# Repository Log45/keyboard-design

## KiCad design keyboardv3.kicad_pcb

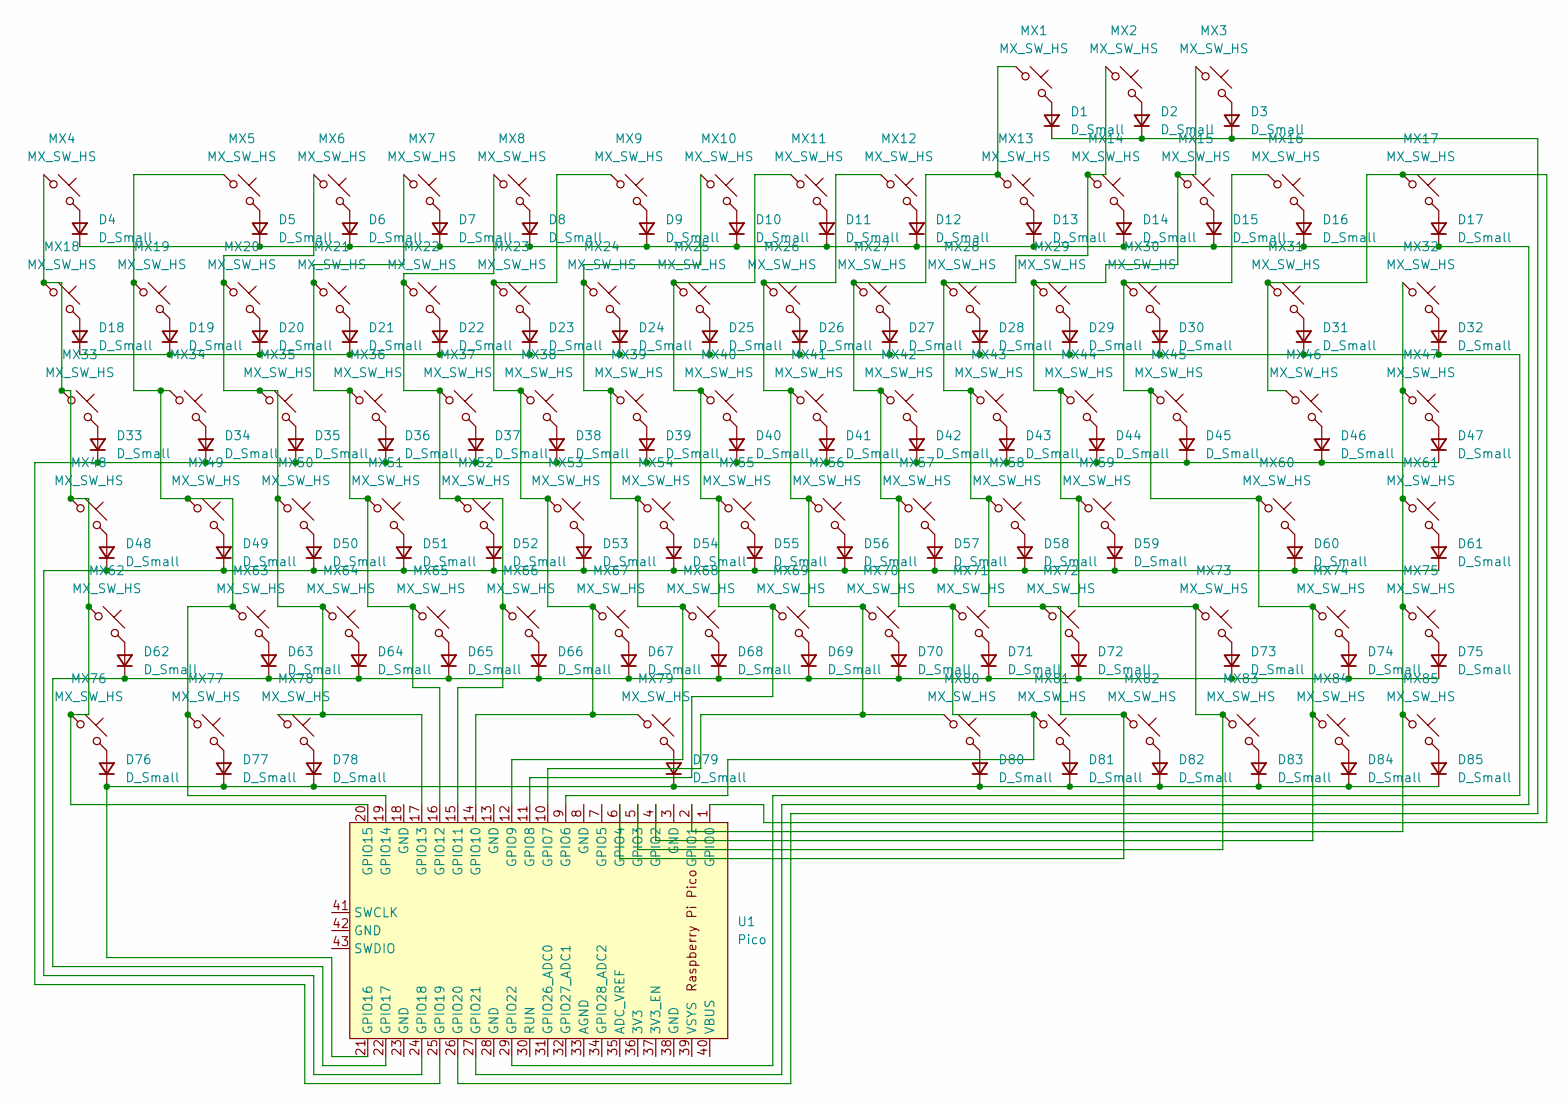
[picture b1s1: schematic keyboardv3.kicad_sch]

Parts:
D1, D2, D3, D4, D5, D6, D7, D8, D9, D10, D11, D12, D13, D14, D15, D16, D17, D18, D19, D20, D21, D22, D23, D24, D25, D26, D27, D28, D29, D30, D31, D32, D33, D34, D35, D36, D37, D38, D39, D40, D41, D42, D43, D44, D45, D46, D47, D48, D49, D50, D51, D52, D53, D54, D55, D56, D57, D58, D59, D60, D61, D62, D63, D64, D65, D66, D67, D68, D69, D70, D71, D72, D73, D74, D75, D76, D77, D78, D79, D80, D81, D82, D83, D84, D85: D_Small; D_0805_2012Metric_Pad1.15x1.40mm_HandSolder
MX1, MX2, MX3, MX4, MX5, MX6, MX7, MX8, MX9, MX10, MX11, MX12, MX13, MX14, MX15, MX16, MX17, MX18, MX19, MX20, MX21, MX22, MX23, MX24, MX25, MX26, MX27, MX28, MX29, MX30, MX31, MX32, MX34, MX35, MX36, MX37, MX38, MX39, MX40, MX41, MX42, MX43, MX44, MX45, MX47, MX49, MX50, MX51, MX52, MX53, MX54, MX55, MX56, MX57, MX58, MX59, MX60, MX61, MX62, MX63, MX64, MX65, MX66, MX67, MX68, MX69, MX70, MX71, MX72, MX74, MX75, MX77, MX78, MX79, MX80, MX81, MX82, MX83, MX84, MX85: MX_SW_HS; SW_MX_HS_1u
MX33, MX46: MX_SW_HS; SW_MX_HS_1.5u
MX48, MX73, MX76: MX_SW_HS; SW_MX_HS_1.75u
U1: Pico; RPi_Pico_SMD_TH

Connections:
unnamed: D1.2 (A), MX1.2
unnamed: D1.1 (K), D2.1 (K), D3.1 (K), U1.26 (GPIO20)
unnamed: D2.2 (A), MX2.2
unnamed: D3.2 (A), MX3.2
unnamed: D4.2 (A), MX4.2
unnamed: D5.2 (A), MX5.2
unnamed: D6.2 (A), MX6.2
unnamed: D7.2 (A), MX7.2
unnamed: D8.2 (A), MX8.2
unnamed: D9.2 (A), MX9.2
unnamed: D10.2 (A), MX10.2
unnamed: D4.1 (K), D5.1 (K), D6.1 (K), D7.1 (K), D8.1 (K), D9.1 (K), D10.1 (K), D11.1 (K), D12.1 (K), D13.1 (K), D14.1 (K), D15.1 (K), D16.1 (K), D17.1 (K), U1.27 (GPIO21)
unnamed: D11.2 (A), MX11.2
unnamed: D12.2 (A), MX12.2
unnamed: D13.2 (A), MX13.2
unnamed: D14.2 (A), MX14.2
unnamed: D15.2 (A), MX15.2
unnamed: D16.2 (A), MX16.2
unnamed: D17.2 (A), MX17.2
unnamed: D18.2 (A), MX18.2
unnamed: D18.1 (K), D19.1 (K), D20.1 (K), D21.1 (K), D22.1 (K), D23.1 (K), D24.1 (K), D25.1 (K), D26.1 (K), D27.1 (K), D28.1 (K), D29.1 (K), D30.1 (K), D31.1 (K), D32.1 (K), U1.29 (GPIO22)
unnamed: D19.2 (A), MX19.2
unnamed: D20.2 (A), MX20.2
unnamed: D21.2 (A), MX21.2
unnamed: D22.2 (A), MX22.2
unnamed: D23.2 (A), MX23.2
unnamed: D24.2 (A), MX24.2
unnamed: D25.2 (A), MX25.2
unnamed: D26.2 (A), MX26.2
unnamed: D27.2 (A), MX27.2
unnamed: D28.2 (A), MX28.2
unnamed: D29.2 (A), MX29.2
unnamed: D30.2 (A), MX30.2
unnamed 33: D31.2 (A), MX31.2; also elsewhere on the board
unnamed: D32.2 (A), MX32.2
unnamed: D33.2 (A), MX33.2
unnamed: D33.1 (K), D34.1 (K), D35.1 (K), D36.1 (K), D37.1 (K), D38.1 (K), D39.1 (K), D40.1 (K), D41.1 (K), D42.1 (K), D43.1 (K), D44.1 (K), D45.1 (K), D46.1 (K), D47.1 (K), U1.25 (GPIO19)
unnamed: D34.2 (A), MX34.2
unnamed: D35.2 (A), MX35.2
unnamed: D36.2 (A), MX36.2
unnamed: D37.2 (A), MX37.2
unnamed: D38.2 (A), MX38.2
unnamed: D39.2 (A), MX39.2
unnamed: D40.2 (A), MX40.2
unnamed: D41.2 (A), MX41.2
unnamed: D42.2 (A), MX42.2
unnamed: D43.2 (A), MX43.2
unnamed: D44.2 (A), MX44.2
unnamed: D45.2 (A), MX45.2
unnamed: D46.2 (A), MX46.2
unnamed: D47.2 (A), MX47.2
unnamed: D48.2 (A), MX48.2
unnamed: D48.1 (K), D49.1 (K), D50.1 (K), D51.1 (K), D52.1 (K), D53.1 (K), D54.1 (K), D55.1 (K), D56.1 (K), D57.1 (K), D58.1 (K), D59.1 (K), D60.1 (K), D61.1 (K), U1.24 (GPIO18)
unnamed: D49.2 (A), MX49.2
unnamed: D50.2 (A), MX50.2
unnamed: D51.2 (A), MX51.2
unnamed: D52.2 (A), MX52.2
unnamed: D53.2 (A), MX53.2
unnamed: D54.2 (A), MX54.2
unnamed: D55.2 (A), MX55.2
unnamed: D56.2 (A), MX56.2
unnamed: D57.2 (A), MX57.2
unnamed: D58.2 (A), MX58.2
unnamed: D59.2 (A), MX59.2
unnamed 64: D60.2 (A), MX60.2; also elsewhere on the board
unnamed: D61.2 (A), MX61.2
unnamed: D62.2 (A), MX62.2
unnamed: D62.1 (K), D63.1 (K), D64.1 (K), D65.1 (K), D66.1 (K), D67.1 (K), D68.1 (K), D69.1 (K), D70.1 (K), D71.1 (K), D72.1 (K), D73.1 (K), D74.1 (K), D75.1 (K), U1.22 (GPIO17)
unnamed: D63.2 (A), MX63.2
unnamed: D64.2 (A), MX64.2
unnamed: D65.2 (A), MX65.2
unnamed: D66.2 (A), MX66.2
unnamed: D67.2 (A), MX67.2
unnamed: D68.2 (A), MX68.2
unnamed: D69.2 (A), MX69.2
unnamed: D70.2 (A), MX70.2
unnamed: D71.2 (A), MX71.2
unnamed: D72.2 (A), MX72.2
unnamed: D73.2 (A), MX73.2
unnamed: D74.2 (A), MX74.2
unnamed: D75.2 (A), MX75.2
unnamed: D76.2 (A), MX76.2
unnamed: D76.1 (K), D77.1 (K), D78.1 (K), D79.1 (K), D80.1 (K), D81.1 (K), D82.1 (K), D83.1 (K), D84.1 (K), D85.1 (K), U1.21 (GPIO16)
unnamed: D77.2 (A), MX77.2
unnamed: D78.2 (A), MX78.2
unnamed: D79.2 (A), MX79.2
unnamed: D80.2 (A), MX80.2
unnamed: D81.2 (A), MX81.2
unnamed: D82.2 (A), MX82.2
unnamed: D83.2 (A), MX83.2
unnamed: D84.2 (A), MX84.2
unnamed: D85.2 (A), MX85.2
unnamed 92: MX17.1, MX31.1, MX46.1, U1.1 (GPIO0); also elsewhere on the board
unnamed: MX32.1, MX47.1, MX61.1, MX75.1, MX85.1, U1.2 (GPIO1)
unnamed 94: MX16.1, MX30.1, MX45.1, MX60.1, MX74.1, MX84.1, U1.4 (GPIO2); also elsewhere on the board
unnamed: MX3.1, MX15.1, MX29.1, MX44.1, MX59.1, MX73.1, MX83.1, U1.5 (GPIO3)
unnamed: MX2.1, MX14.1, MX28.1, MX43.1, MX58.1, MX72.1, MX82.1, U1.6 (GPIO4)
unnamed: MX1.1, MX13.1, MX27.1, MX42.1, MX57.1, MX71.1, MX81.1, U1.9 (GPIO6)
unnamed: MX12.1, MX26.1, MX41.1, MX56.1, MX70.1, MX80.1, U1.10 (GPIO7)
unnamed: MX11.1, MX25.1, MX40.1, MX55.1, MX69.1, U1.11 (GPIO8)
unnamed: MX10.1, MX24.1, MX39.1, MX54.1, MX68.1, U1.12 (GPIO9)
unnamed: MX9.1, MX23.1, MX38.1, MX53.1, MX67.1, MX79.1, U1.14 (GPIO10)
unnamed: MX8.1, MX22.1, MX37.1, MX52.1, MX66.1, U1.15 (GPIO11)
unnamed: MX7.1, MX21.1, MX36.1, MX51.1, MX65.1, U1.16 (GPIO12)
unnamed: MX6.1, MX20.1, MX35.1, MX50.1, MX64.1, MX78.1, U1.17 (GPIO13)
unnamed: MX5.1, MX19.1, MX34.1, MX49.1, MX63.1, MX77.1, U1.19 (GPIO14)
unnamed: MX4.1, MX18.1, MX33.1, MX48.1, MX62.1, MX76.1, U1.20 (GPIO15)

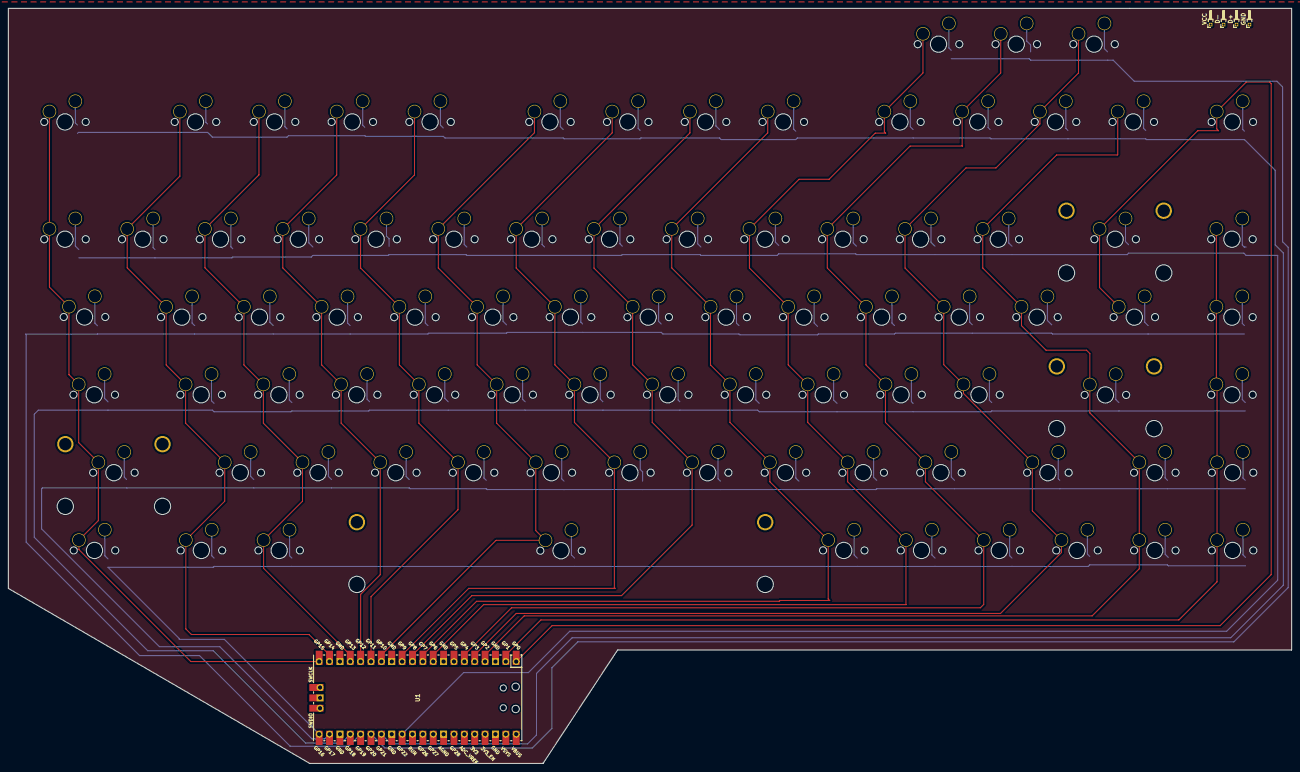
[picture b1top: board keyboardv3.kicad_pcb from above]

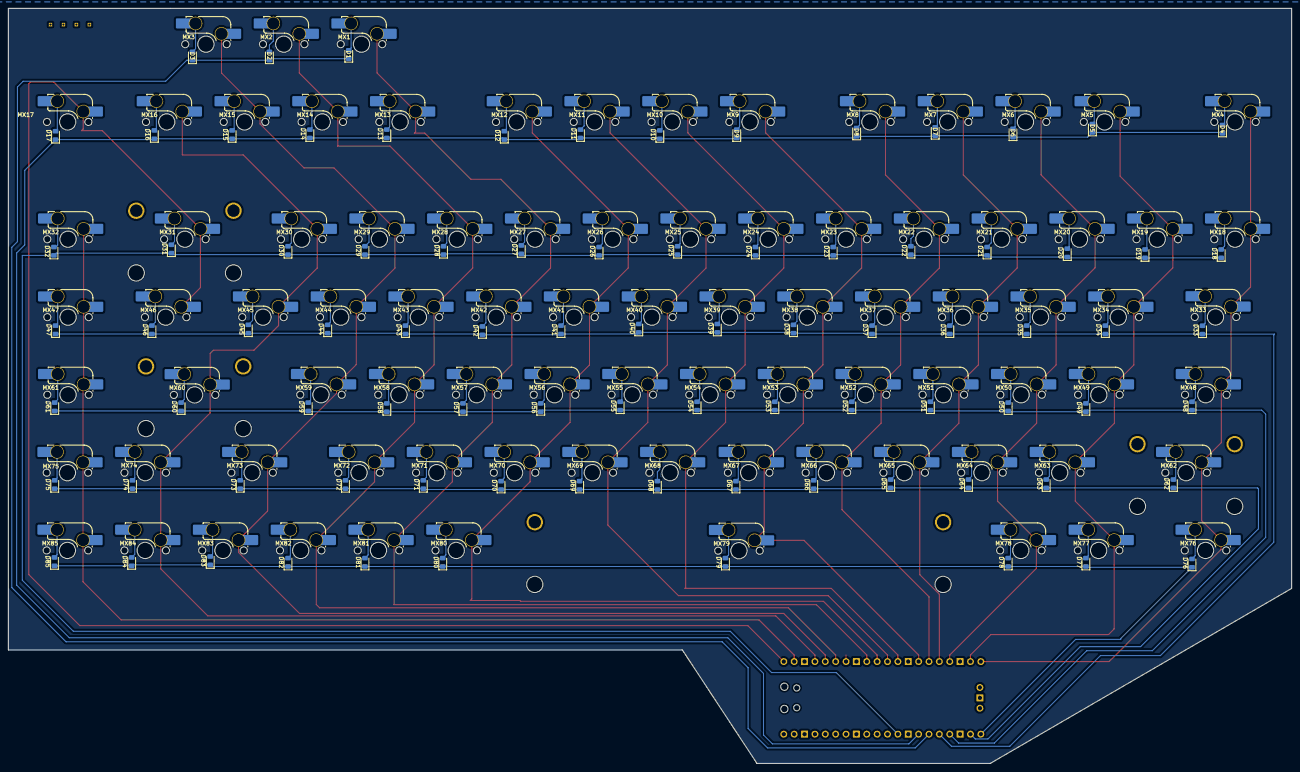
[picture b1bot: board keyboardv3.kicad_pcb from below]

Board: 2 copper layers, 314.3 x 184.9 mm, 178 parts (170 on the bottom side), 107 nets.

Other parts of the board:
D+: PinHeader_1x01_P1.00mm_Horizontal
D-: PinHeader_1x01_P1.00mm_Horizontal
GND: PinHeader_1x01_P1.00mm_Horizontal
MX31#2, MX60#3: MX_SW_HS; SW_MX_HS_1u
MX60#2: MX_SW_HS; STAB_MX_P_2.25u
VCC: PinHeader_1x01_P1.00mm_Horizontal

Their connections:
unnamed 33: MX31#2.2; also elsewhere on the board
unnamed 64: MX60#3.2; also elsewhere on the board
unnamed 92: MX31#2.1; also elsewhere on the board
unnamed 94: MX60#3.1; also elsewhere on the board

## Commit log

2024-03-10 Code for the MacroPad example board
2024-03-10 Tweaked initial full keyboard design diodes
    Switched from 0805 smd diodes to DO-35 through-hole diodes to allow for easier assembly
2024-03-10 Examples and code for full size
    This all should give a working keyboard, though it will definitely have its quirks due to current lack of key rollover.
